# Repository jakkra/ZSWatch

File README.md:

# [zswatch.dev](https://zswatch.dev/)

<div align="center">

<sub>
  ZSWatch v4 CNC:ed Stainless Steel (left), Clear Resin 3D print (right)
</sub>
</div>

## Table of content

- [ZSWatch](#zswatch)
  - [Table of content](#table-of-content)
  - [About](#about)
  - [Features](#features)
    - [Hardware](#hardware)
      - [PCB](#pcb)
    - [Software](#software)
    - [Watchfaces](#watchfaces)
    - [Smartphone communication](#smartphone-communication)
      - [Pairing](#pairing)
      - [Android phone communication](#android-phone-communication)
      - [iOS device communication](#ios-device-communication)
    - [Enclosure/Casing](#enclosurecasing)
    - [Upcomming features](#upcomming-features)
  - [Charger/Dock](#chargerdock)
  - [Demos](#demos)
  - [Building or getting one](#building-or-getting-one)
  - [Environment, Compiling and running the code](#environment-compiling-and-running-the-code)
  - [Writing apps for the Application Manager](#writing-apps-for-the-application-manager)
  - [Licence GPL-3.0](#licence-gpl-30)
  - [Thanks](#thanks)
  - [Miscellaneous stuff](#miscellaneous-stuff)

## About

Smartwatch built from scratch, both hardware and software. Built on the [Zephyr™ Project](https://www.zephyrproject.org/) RTOS, hence the name **ZSWatch** - *Zephyr Smartwatch*.

<kbd></kbd>

https://github.com/jakkra/ZSWatch/assets/4318648/ec1a94fd-a682-4559-9e68-f3e5bfcbe682

## Features

### Hardware

- nRF5340 BLE chip ([u-blox NORA-B10 module](https://www.u-blox.com/en/product/nora-b1-series-open-cpu))
  - 128 MHz Dual core
  - 512 KB RAM
  - 1 MB Flash
  - 30 MHz SPI for display
- [240x240 round display](https://www.buydisplay.com/catalog/product/view/id/1849/s/240x240-round-ips-tft-lcd-display-1-28-capacitive-touch-circle-screen/) with touch screen
- IMU [Bosch BMI270](https://www.bosch-sensortec.com/media/boschsensortec/downloads/datasheets/bst-bmi270-ds000.pdf), with this one it's possible to do many fancy things such as navigation using gestures and the typical smartwatch wakeup by moving the arm so the display is viewable
- Bosch [BME688](https://www.bosch-sensortec.com/products/environmental-sensors/gas-sensors/bme688/) Environmental sensor with AI
- Bosch [BMP581](https://www.bosch-sensortec.com/products/environmental-sensors/pressure-sensors/bmp581/) High performance pressure sensor accuracy in units of ~20cm's
- ST [LIS2MDLTR](https://www.st.com/resource/en/datasheet/lis2mdl.pdf) Magnetometer
- Macronix [MX25U51245GZ4I00](https://www.mouser.de/datasheet/2/819/MX25U51245G_2c_1_8V_2c_512Mb_2c_v1_4-3371129.pdf) 64 MB external flash
- Broadcom [APDS-9306-065](https://docs.broadcom.com/docs/AV02-4755EN) Light Sensor for automatic brightness control
- Micro Crystal [RV-8263-C8](https://www.microcrystal.com/en/products/real-time-clock-rtc-modules/rv-8263-c8) RTC for time keeping and alarm functions
- Knowles [SPK0641HT4H-1](https://www.knowles.com/docs/default-source/model-downloads/spk0641ht4h-1-rev-a.pdf) I2S microphone for audio recording
- Nordic [nPM1300](https://docs.nordicsemi.com/category/npm1300-category) PMIC for power and system management
- Texas Instruments [TS3USB221A](https://www.ti.com/lit/ds/symlink/ts3usb221a.pdf?HQS=dis-mous-null-mousermode-dsf-pf-null-wwe&ts=1695813909306&ref_url=https%253A%252F%252Feu.mouser.com%252F) USB / SWD switch to provide a USB or SWD interface on the dock connector
- Option to not mount sensors to save BOM cost

#### PCB

A 4-layer board that measures 38mm in diameter is designed in KiCad. More info [here](https://github.com/jakkra/ZSWatch-HW).

<kbd></kbd>

### Software

- Bluetooth LE communications with [GadgetBridge](https://codeberg.org/Freeyourgadget/Gadgetbridge) Android app.
- Also support Bluetooth Direction Finding so the watch can act as a tag and is trackable using any [u-blox AoA antenna board](https://www.u-blox.com/en/product/ant-b10-antenna-board)
- Multiple Watchfaces showing:
  - Standard stuff such as time, date, battery
  - Weather
  - Step count
  - Number of unread notifications
  - Environmental data
  - ...
- Pop-up notifications
- [Application picker and app concept](#writing-apps-for-the-application-manager)
  - [Setting menu system, with easy extendability](app/src/applications/settings/)
  - [Music control app](app/src/applications/music_control/)
  - [Settings app](app/src/applications/settings/)
  - [Compass app](app/src/applications/compass/)
  - etc.
- Step counting
- Gestures
- And much more
...

### Watchfaces

The watch supports different watchfaces which can be changed dynamically. The watch also supports ESP32 watchfaces from [Felix Biego](https://github.com/fbiego). Please checkout [this](https://github.com/Kampi/esp32-lvgl-watchface) fork for more informations.

### Smartphone communication

#### Pairing

- In the watch go to `Settings` -> `Bluetooth` -> `Enable pairing`
- Now go reconnect to the watch from the Gadgetbridge app
- You should now be paired

#### Android phone communication

Fortunately, there is a great Android app called [GadgetBridge](https://codeberg.org/Freeyourgadget) that handles everything needed on the phone side, such as notifications management, music control and so much more. The ZSWatch right now pretends to be one of the supported Smart Watches in Gadgetbridge, following the same API as it does. In the future there may be a point in adding native support, we'll see.

#### iOS device communication

Apple exposes [Apple Notification Center Service](https://developer.apple.com/library/archive/documentation/CoreBluetooth/Reference/AppleNotificationCenterServiceSpecification/Specification/Specification.html) GATT server which handles notifications management on the phone side, music control is done in the same fashion using [Apple Media Service](https://developer.apple.com/library/archive/documentation/CoreBluetooth/Reference/AppleMediaService_Reference/Specification/Specification.html)... The ZSWatch communicates straight to the iOS with no extra Apps.

### Enclosure/Casing

3D printed casing with 3D printed buttons, option CNC:able casing in metal.

### Upcomming features

There are almost endless possibilities for features that could be implemented, see [here for full progress](https://github.com/users/jakkra/projects/1) and in GitHub issues.

## Charger/Dock

Option with and without onboard SEGGER J-Link OB debugger. As the debugger requires a license, this will only be available as part of a kit.

See more at [here](https://github.com/jakkra/ZSWatch-Dock).

## Demos

- [HTTP requests over BLE through Gadgetbridge](https://github.com/jakkra/ZSWatch/assets/4318648/12d6e754-ceb3-4efd-9a75-d207aaeb0e82)
- [Watchfaces](https://github.com/jakkra/ZSWatch/assets/4318648/13e43401-1c00-40ab-866f-e6518e61940d)

## Building or getting one

- Head over to the hardware repos for the [PCB](https://github.com/jakkra/ZSWatch-HW) and the [Dock](https://github.com/jakkra/ZSWatch-Dock) for information about ordering the PCBs and assembly from PCBWay
- Go to the [Wiki](https://github.com/jakkra/ZSWatch/wiki/Case,-3D-printing-and-assembling) for information how to print parts and assemble ZSWatch

Some things are still in progress:

- [Building instructions in Wiki](https://github.com/jakkra/ZSWatch/wiki/Case,-3D-printing-and-assembling)
- Dock casing

If you are interested in a kit or want to get notified when the missing parts above are resolved, fill in your **[mail here](https://zswatch.dev/)** and we'll send a reminder when it's ready.

**Or** if you want to get notified for releases and when the missing parts are finished simply press the `Watch` button (next to Fork and Star) -> `Custom` -> `Releases` and you will see in your feed when it's officially released.

## Environment, Compiling and running the code

See [Wiki page about Start Developing](https://github.com/jakkra/ZSWatch/wiki/Start-Developing).

## Writing apps for the Application Manager

See [Wiki page about apps](https://github.com/jakkra/ZSWatch/wiki/Apps).

## Licence GPL-3.0

The main difference from MIT is now that if anyone wants to build something more with this, then they need to also open source their changes back to the project, which I think this is fair. This is so everyone can benefit from those improvements. If you think this is wrong free to contact me and I'm open to change the LICENCE.

## Thanks

### Funding

This project is partly funded through [NGI0 Commons Fund](https://nlnet.nl/commonsfund), a fund established by [NLnet](https://nlnet.nl) with financial support from the European Commission's [Next Generation Internet](https://ngi.eu) program. Learn more at the [NLnet project page](https://nlnet.nl/project/ZSWatch).

### Support

<p align="left">

</p>

**PCBWay** for sponsoring the manufacturing and assembly of some prototype PCBs. PCBWay is the recommended manufacturer for PCBs and assembly of ZSWatch.

**SEGGER** for supporting SEGGER-OB licenses that make the dock a fully functional programmer and debugger for ZSWatch. Thanks to this, the project is much more approachable for persons without a J-Link debugger, letting them have full development and debugging capabilities.

## Miscellaneous stuff

- [Watch my presentation at Zephyr Developer Summit 2023](https://www.youtube.com/watch?v=MmCzV0jV9hs)

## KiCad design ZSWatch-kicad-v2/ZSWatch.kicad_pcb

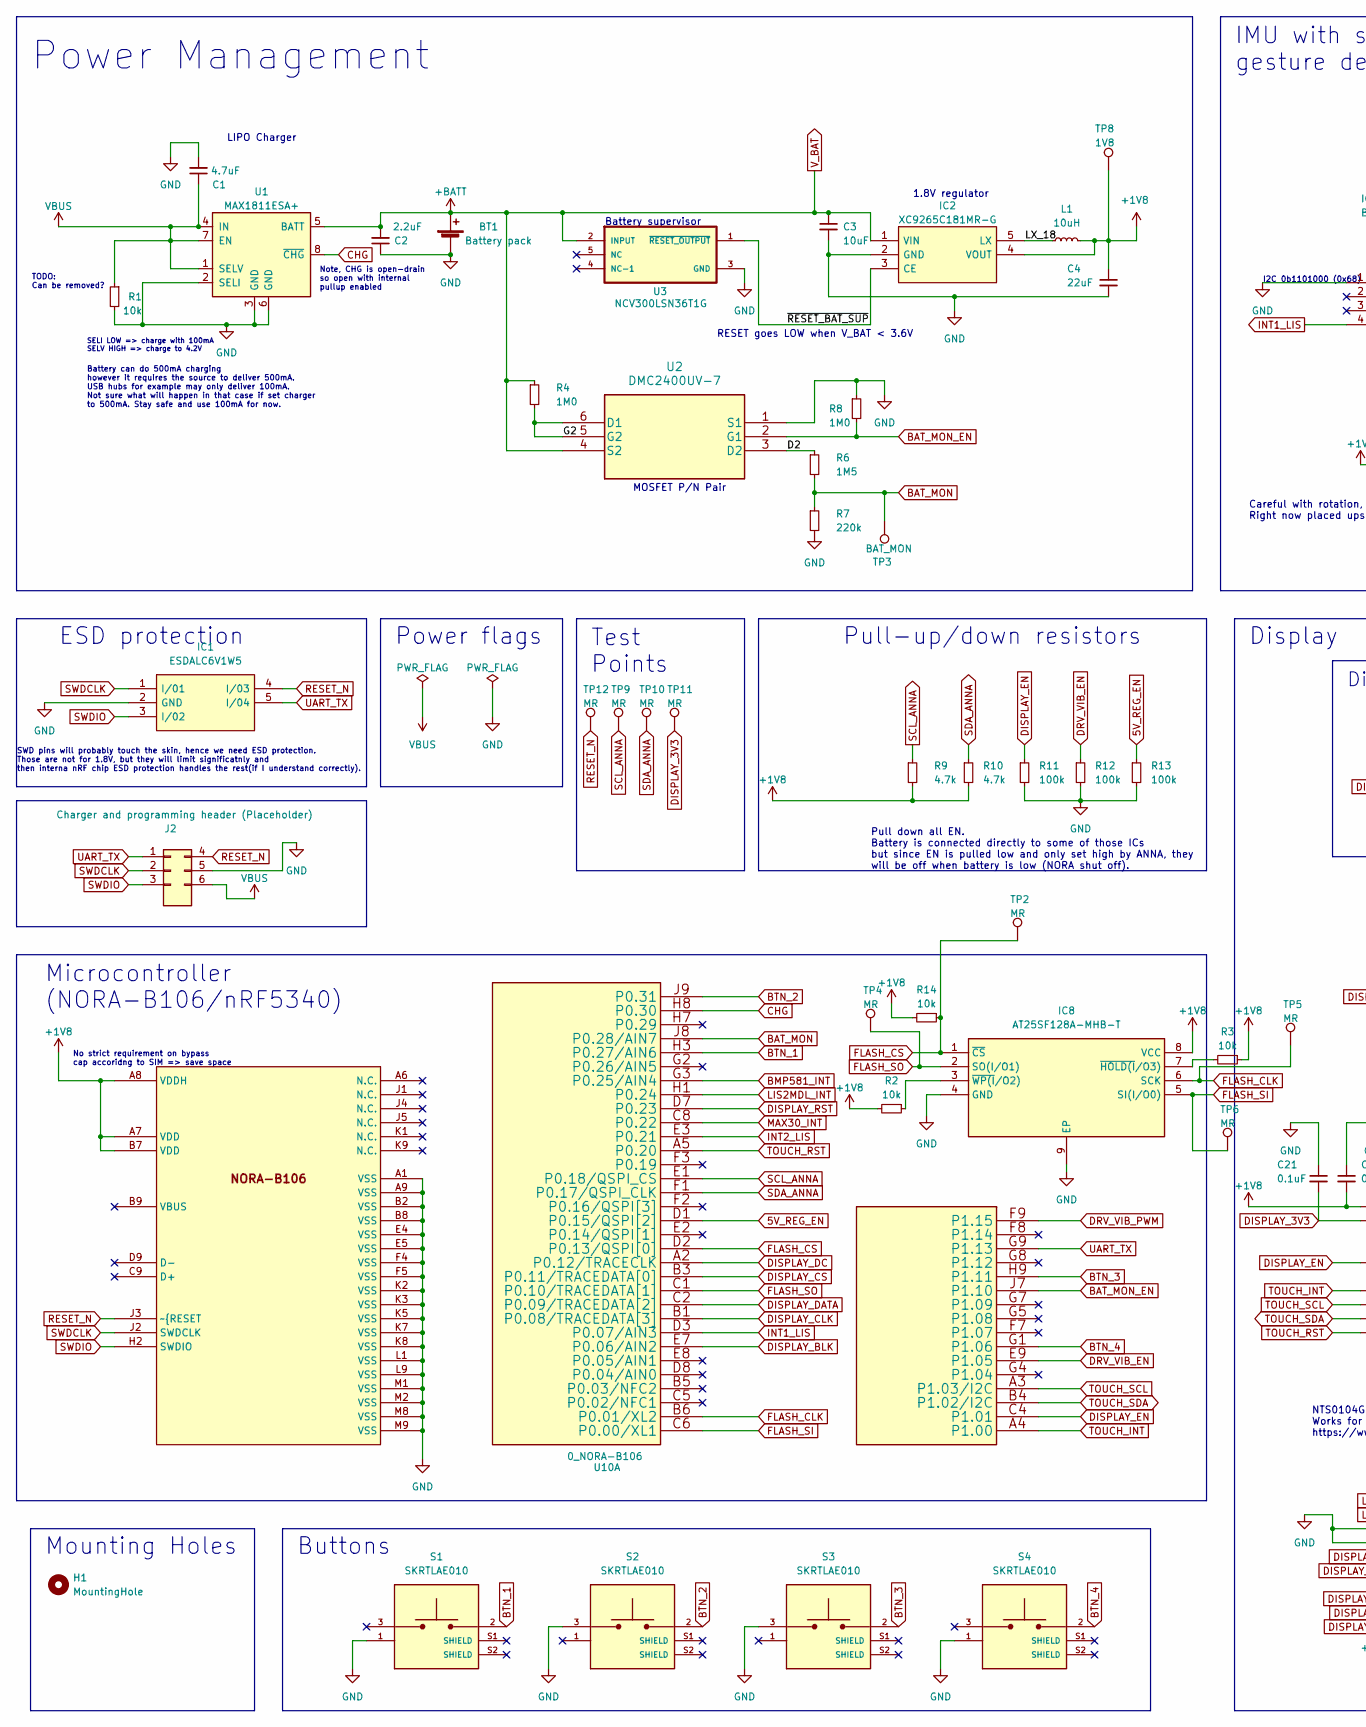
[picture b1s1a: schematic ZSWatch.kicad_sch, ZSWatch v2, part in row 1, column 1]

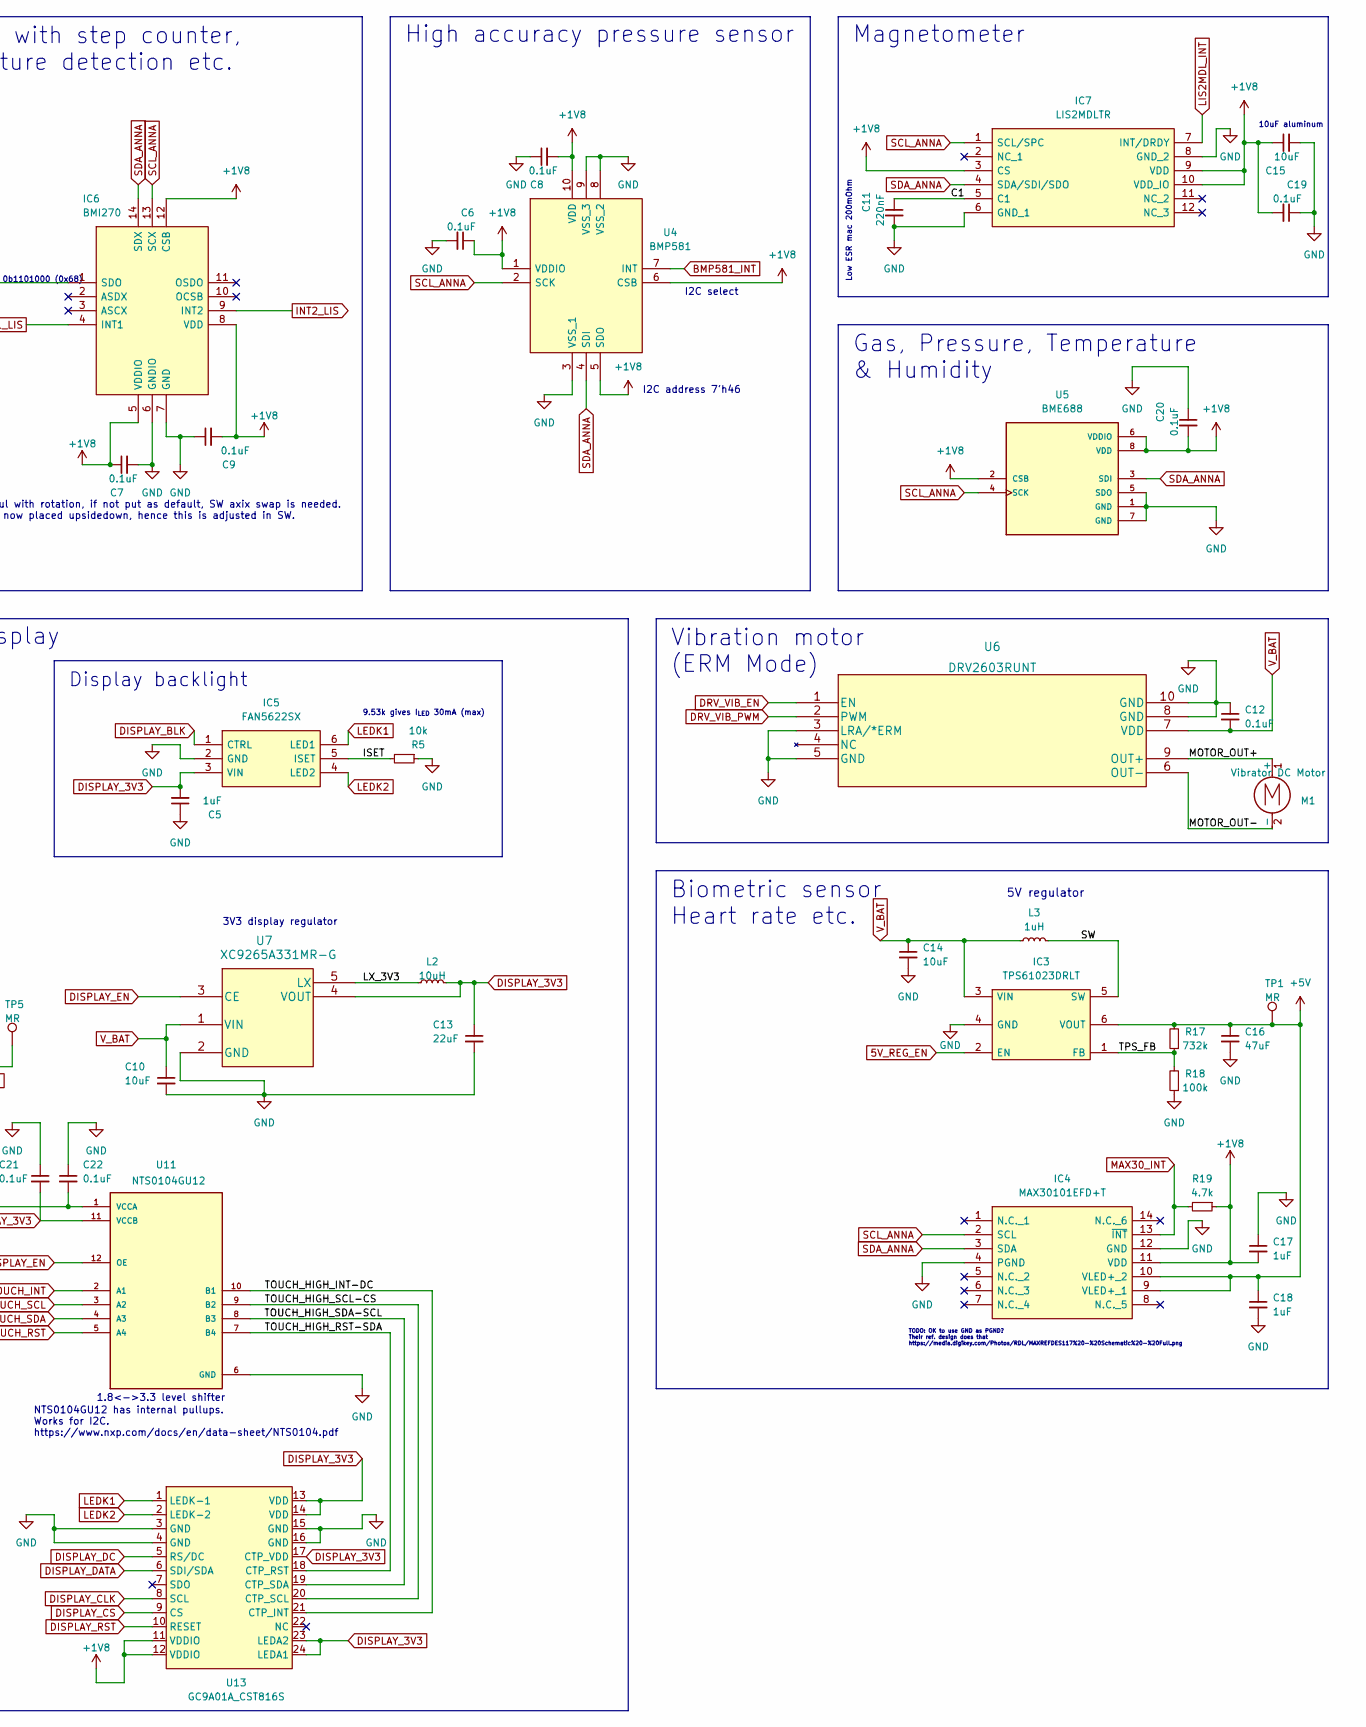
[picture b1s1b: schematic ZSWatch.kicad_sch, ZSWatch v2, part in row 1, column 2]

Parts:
BT1: Battery pack; SolderWire-0.1sqmm_1x02_P3.6mm_D0.4mm_OD1mm
C1: 4.7uF; C_0603_1608Metric
C2: 2.2uF; C_0603_1608Metric
C3, C10, C14, C15: 10uF; C_0603_1608Metric
C4, C13: 22uF; C_0603_1608Metric
C5, C17, C18: 1uF; C_0603_1608Metric
C6, C7, C8, C9, C12, C19, C20, C21, C22: 0.1uF; C_0603_1608Metric
C11: 220nF; C_0603_1608Metric
C16: 47uF; C_0603_1608Metric
H1: MountingHole; MountingHole_3.5mm_Pad_Via
IC1: ESDALC6V1W5; SOT65P210X110-5L; Mouser Part Number 511-ESDALC6V1W5
IC2: XC9265C181MR-G; SOT95P280X130-5N; Mouser Part Number 865-XC9265C181MR-G
IC3: TPS61023DRLT; SOTFL50P160X60-6N; Mouser Part Number 595-TPS61023DRLT
IC4: MAX30101EFD+T; 14-LEAD-OESIP; Mouser Part Number 700-MAX30101EFD+T
IC5: FAN5622SX; SOT95P280X110-6N; Mouser Part Number 512-FAN5622SX
IC6: BMI270; QFN50P300X250X87-14N; Mouser Part Number 262-BMI270
IC7: LIS2MDLTR; LGA-12; Mouser Part Number 511-LIS2MDLTR
IC8: AT25SF128A-MHB-T; SON127P600X500X60-9N-D; Manufacturer_Part_Number AT25SF128A-MHB-T; Mouser Part Number 988-AT25SF128A-MHB-T
J2: Charger and programming header (Placeholder); rtlecs-6-pin-2-54
L1, L2: 10uH; L_0603_1608Metric
L3: 1uH; L_0603_1608Metric
M1: Vibrator DC Motor; TestPoint_2Pads_Pitch2.54mm_Drill0.8mm
R1, R3, R5: 10k; R_0603_1608Metric
R2, R14: 10k; R_0402_1005Metric
R4, R8: 1M0; R_0603_1608Metric
R6: 1M5; R_0603_1608Metric
R7: 220k; R_0603_1608Metric
R9, R10, R19: 4.7k; R_0603_1608Metric
R11, R12, R13, R18: 100k; R_0603_1608Metric
R17: 732k; R_0603_1608Metric
S1, S2, S3, S4: SKRTLAE010; SW_SKRTLAE010; PARTREV --
TP1, TP2, TP4, TP5, TP6, TP9, TP10, TP11, TP12: MR; TestPoint_Pad_D1.0mm
TP3: BAT_MON; TestPoint_Pad_D1.0mm
TP8: 1V8; TestPoint_Pad_D1.0mm
U1: MAX1811ESA+; SOIC127P600X175-8N
U2: DMC2400UV-7
U3: NCV300LSN36T1G; SOT95P275X110-5N
U4: BMP581; Mouser Part Number 262-BMP581
U5: BME688; IC_BME688; PARTREV 1.0
U6: DRV2603RUNT
U7: XC9265A331MR-G; SOT95P280X130-5N
U10: 0_NORA-B106; NORA_LGA82R_1430X1040X180_ANT; MANUFACTURER P/N NORA-B106-00B
U11: NTS0104GU12; HPA01164RUTR; PARTREV 4210580/C 06/12
U13: GC9A01A_CST816S; ER-24F24-04

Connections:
5V_REG_EN: IC3.2 (EN), R13.1, U10.D1 (P0.15/QSPI[2])
+1V8: C4.1, C6.1, C7.1, C8.2, C9.2, C15.1, C17.2, C19.2, C20.2, C22.2, IC2.4 (VOUT), IC4.11 (VDD), IC6.5 (VDDIO), IC6.8 (VDD), IC6.12 (CSB), IC7.3 (CS), IC7.9 (VDD), IC7.10 (VDD_IO), IC8.8 (VCC), L1.2, R2.2, R3.1, R9.2, R10.2, R14.2, R19.1, TP8.1, U4.1 (VDDIO), U4.5 (SDO), U4.6 (CSB), U4.10 (VDD), U5.2 (CSB), U5.6 (VDDIO), U5.8 (VDD), U10.A7 (VDD), U10.A8 (VDDH), U10.B7 (VDD), U11.1 (VCCA), U13.11 (VDDIO), U13.12 (VDDIO)
+5V: C16.1, C18.1, IC3.6 (VOUT), IC4.9 (VLED+_1), IC4.10 (VLED+_2), R17.2, TP1.1
/C1: C11.1, IC7.5 (C1)
/D2: R6.1, U2.3 (D2)
/G2: R4.2, U2.5 (G2), U2.6 (D1)
/ISET: IC5.5 (ISET), R5.2
/LX_3V3: L2.1, U7.5 (LX)
/LX_18: IC2.5 (LX), L1.1
/MOTOR_OUT+: M1.1 (+), U6.9 (OUT+)
/MOTOR_OUT-: M1.2 (-), U6.6 (OUT-)
/SW: IC3.5 (SW), L3.2
/TOUCH_HIGH_INT-DC: U11.10 (B1), U13.21 (CTP_INT)
/TOUCH_HIGH_RST-SDA: U11.7 (B4), U13.18 (CTP_RST)
/TOUCH_HIGH_SCL-CS: U11.9 (B2), U13.20 (CTP_SCL)
/TOUCH_HIGH_SDA-SCL: U11.8 (B3), U13.19 (CTP_SDA)
/TPS_FB: IC3.1 (FB), R17.1, R18.2
/~RESET_BAT_SUP: IC2.3 (CE), U3.1 (~RESET_OUTPUT)
BAT_MON: R6.2, R7.1, TP3.1, U10.J8 (P0.28/AIN7)
BAT_MON_EN: R8.2, U2.2 (G1), U10.J7 (P1.10)
BMP581_INT: U4.7 (INT), U10.G3 (P0.25/AIN4)
BTN_1: S1.2, U10.H3 (P0.27/AIN6)
BTN_2: S2.2, U10.J9 (P0.31)
BTN_3: S3.2, U10.H9 (P1.11)
BTN_4: S4.2, U10.G1 (P1.06)
CHG: U1.8 (~CHG), U10.H8 (P0.30)
DISPLAY_3V3: C5.2, C13.1, C21.2, IC5.3 (VIN), L2.2, TP11.1, U7.4 (VOUT), U11.11 (VCCB), U13.13 (VDD), U13.14 (VDD), U13.17 (CTP_VDD), U13.23 (LEDA2), U13.24 (LEDA1)
DISPLAY_BLK: IC5.1 (CTRL), U10.E7 (P0.06/AIN2)
DISPLAY_CLK: U10.B1 (P0.08/TRACEDATA[3]), U13.8 (SCL)
DISPLAY_CS: U10.B3 (P0.11/TRACEDATA[0]), U13.9 (CS)
DISPLAY_DATA: U10.C2 (P0.09/TRACEDATA[2]), U13.6 (SDI/SDA)
DISPLAY_DC: U10.A2 (P0.12/TRACECLK), U13.5 (RS/DC)
DISPLAY_EN: R11.1, U7.3 (CE), U10.C4 (P1.01), U11.12 (OE)
DISPLAY_RST: U10.D7 (P0.23), U13.10 (RESET)
DRV_VIB_EN: R12.1, U6.1 (EN), U10.E9 (P1.05)
DRV_VIB_PWM: U6.2 (PWM), U10.F9 (P1.15)
FLASH_CLK: IC8.6 (SCK), TP5.1, U10.B6 (P0.01/XL2)
FLASH_CS: IC8.1 (~CS), R14.1, TP2.1, U10.D2 (P0.13/QSPI[0])
FLASH_SI: IC8.5 (SI(I/O0)), TP6.1, U10.C6 (P0.00/XL1)
FLASH_SO: IC8.2 (SO(I/O1)), TP4.1, U10.C1 (P0.10/TRACEDATA[1])
GND: BT1.2 (-), C1.2, C2.1, C3.2, C4.2, C5.1, C6.2, C7.2, C8.1, C9.1, C10.2, C11.2, C12.1, C13.2, C14.2, C15.2, C16.2, C17.1, C18.2, C19.1, C20.1, C21.1, C22.1, IC1.2 (GND), IC2.2 (GND), IC3.4 (GND), IC4.4 (PGND), IC4.12 (GND), IC5.2 (GND), IC6.1 (SDO), IC6.6 (GNDIO), IC6.7 (GND), IC7.6 (GND_1), IC7.8 (GND_2), IC8.4 (GND), IC8.9 (EP), J2.5, R1.2, R5.1, R7.2, R8.1, R11.2, R12.2, R13.2, R18.1, S1.1, S2.3, S3.3, S4.1, U1.2 (SELI), U1.3 (GND), U1.6 (GND), U2.1 (S1), U3.3 (GND), U4.3 (VSS_1), U4.8 (VSS_2), U4.9 (VSS_3), U5.1 (GND), U5.5 (SDO), U5.7 (GND), U6.3 (LRA/*ERM), U6.5 (GND), U6.8 (GND), U6.10 (GND), U7.2 (GND), U10.A1 (VSS), U10.A9 (VSS), U10.B2 (VSS), U10.B8 (VSS), U10.E4 (VSS), U10.E5 (VSS), U10.F4 (VSS), U10.F5 (VSS), U10.K2 (VSS), U10.K3 (VSS), U10.K5 (VSS), U10.K7 (VSS), U10.K8 (VSS), U10.L1 (VSS), U10.L9 (VSS), U10.M1 (VSS), U10.M2 (VSS), U10.M8 (VSS), U10.M9 (VSS), U11.6 (GND), U13.3 (GND), U13.4 (GND), U13.15 (GND), U13.16 (GND)
INT1_LIS: IC6.4 (INT1), U10.D3 (P0.07/AIN3)
INT2_LIS: IC6.9 (INT2), U10.E3 (P0.21)
LEDK1: IC5.6 (LED1), U13.1 (LEDK-1)
LEDK2: IC5.4 (LED2), U13.2 (LEDK-2)
LIS2MDL_INT: IC7.7 (INT/DRDY), U10.H1 (P0.24)
MAX30_INT: IC4.13 (~INT), R19.2, U10.C8 (P0.22)
unnamed: IC8.7 (~HOLD(I/O3)), R3.2
unnamed: IC8.3 (~WP(I/O2)), R2.1
RESET_N: IC1.4 (I/03), J2.4, TP12.1, U10.J3 (~{RESET)
SCL_ANNA: IC4.2 (SCL), IC6.13 (SCX), IC7.1 (SCL/SPC), R9.1, TP9.1, U4.2 (SCK), U5.4 (SCK), U10.E1 (P0.18/QSPI_CS)
SDA_ANNA: IC4.3 (SDA), IC6.14 (SDX), IC7.4 (SDA/SDI/SDO), R10.1, TP10.1, U4.4 (SDI), U5.3 (SDI), U10.F1 (P0.17/QSPI_CLK)
SWDCLK: IC1.1 (I/01), J2.2, U10.J2 (SWDCLK)
SWDIO: IC1.3 (I/02), J2.3, U10.H2 (SWDIO)
TOUCH_INT: U10.A4 (P1.00), U11.2 (A1)
TOUCH_RST: U10.A5 (P0.20), U11.5 (A4)
TOUCH_SCL: U10.A3 (P1.03/I2C), U11.3 (A2)
TOUCH_SDA: U10.B4 (P1.02/I2C), U11.4 (A3)
UART_TX: IC1.5 (I/04), J2.1, U10.G9 (P1.13)
VBUS: C1.1, J2.6, R1.1, U1.1 (SELV), U1.4 (IN), U1.7 (EN)
V_BAT: BT1.1 (+), C2.2, C3.1, C10.1, C12.2, C14.1, IC2.1 (VIN), IC3.3 (VIN), L3.1, R4.1, U1.5 (BATT), U2.4 (S2), U3.2 (INPUT), U6.7 (VDD), U7.1 (VIN)

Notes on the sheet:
Test Points
Display backlight
Battery can do 500mA charging however it requires the source to deliver 500mA. USB hubs for example may only deliver 100mA. Not sure what will happen in that case if set charger to 500mA. Stay safe and use 100mA for now.
1.8<->3.3 level shifter
I2C select
Biometric sensor Heart rate etc.
Gas, Pressure, Temperature & Humidity
High accuracy pressure sensor
3V3 display regulator
Pull-up/down resistors
MOSFET P/N Pair
Power Management
SELI LOW => charge with 100mA SELV HIGH => charge to 4.2V
Battery supervisor
RESET goes LOW when V_BAT < 3.6V
I2C address 7'h46
Low ESR mac 200mOhm
_{I2C 0b1101000 (0x68)}
NTS0104GU12 has internal pullups. Works for I2C. https://www.nxp.com/docs/en/data-sheet/NTS0104.pdf
TODO: Can be removed?
Buttons
Microcontroller (NORA-B106/nRF5340)
TODO: OK to use GND as PGND? Their ref. design does that https://media.digikey.com/Photos/RDL/MAXREFDES117%20-%20Schematic%20-%20Full.png
Note, CHG is open-drain so open with internal pullup enabled
No strict requirement on bypass cap accoridng to SIM => save space
Power flags
9.53k gives I_{LED} 30mA (max)
Magnetometer
SWD pins will probably touch the skin, hence we need ESD protection. Those are not for 1.8V, but they will limit significatnly and then interna nRF chip ESD protection handles the rest(if I understand correctly).
Pull down all EN. Battery is connected directly to some of those ICs but since EN is pulled low and only set high by ANNA, they will be off when battery is low (NORA shut off).
Careful with rotation, if not put as default, SW axix swap is needed. Right now placed upsidedown, hence this is adjusted in SW.
IMU with step counter, gesture detection etc.
LIPO Charger
5V regulator
ESD protection
Vibration motor (ERM Mode)
Mounting Holes
Display
10uF aluminum
1.8V regulator

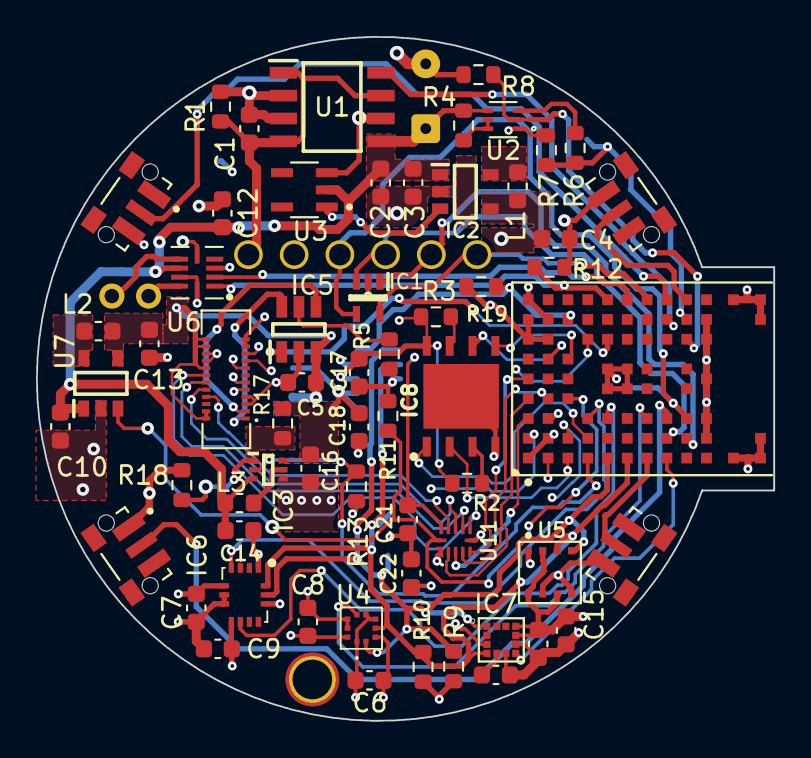
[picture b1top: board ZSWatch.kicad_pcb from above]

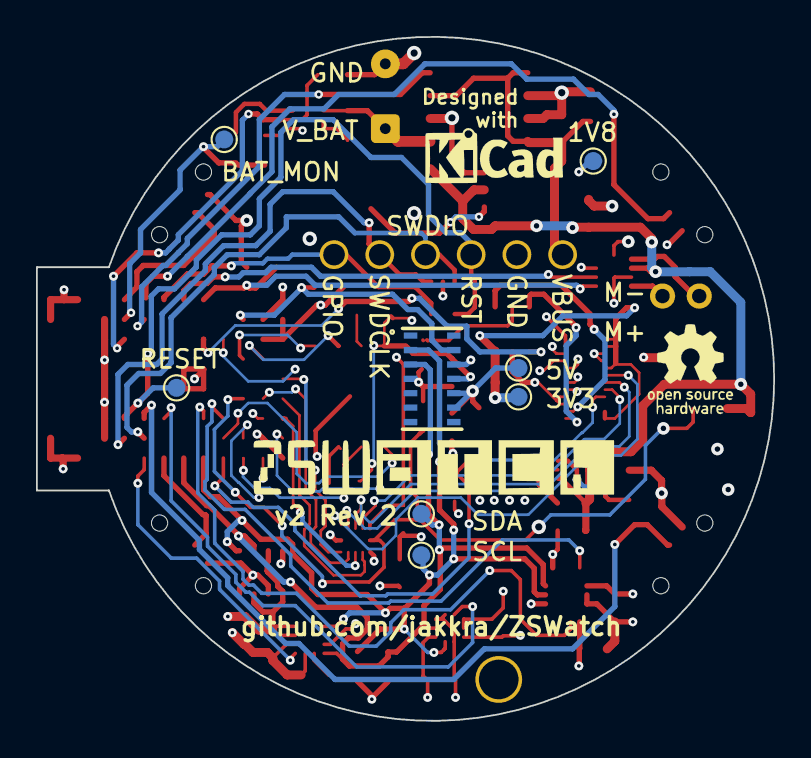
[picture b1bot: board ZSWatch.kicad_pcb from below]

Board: 4 copper layers, 41.0 x 38.0 mm, 73 parts (9 on the bottom side), 61 nets.

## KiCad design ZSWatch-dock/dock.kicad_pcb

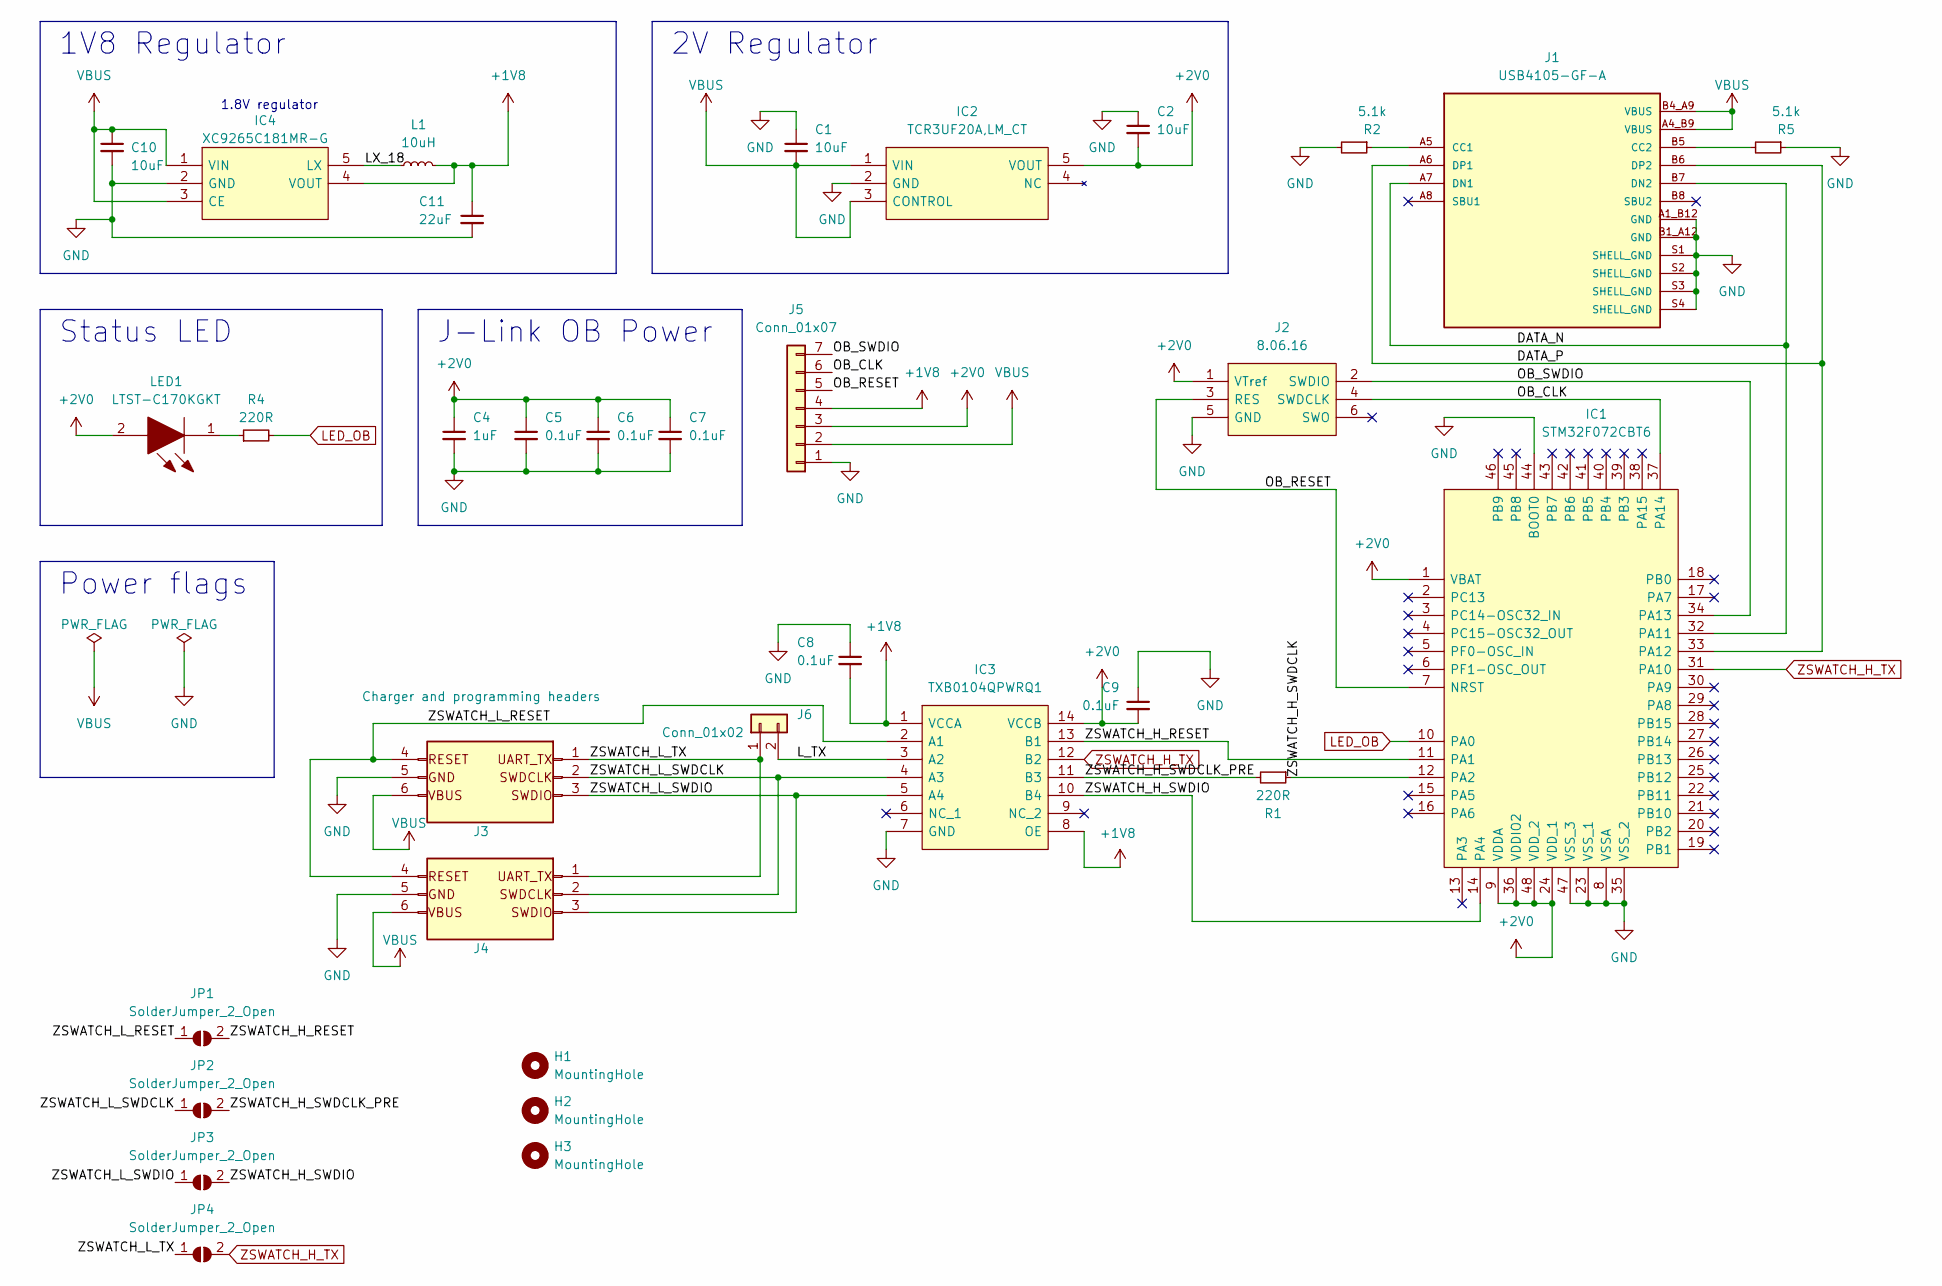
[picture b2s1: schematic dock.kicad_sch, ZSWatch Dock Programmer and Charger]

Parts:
C1, C2, C10: 10uF; C_0603_1608Metric
C4: 1uF; C_0603_1608Metric
C5, C6, C7, C8, C9: 0.1uF; C_0603_1608Metric
C11: 22uF; C_0603_1608Metric
H1, H2, H3: MountingHole; MountingHole_2.2mm_M2
IC1: STM32F072CBT6; QFP50P900X900X160-48N; Mouser Part Number 511-STM32F072CBT6
IC2: TCR3UF20A,LM_CT; TCR3UF20ALMCT; Mouser Part Number 757-TCR3UF20ALMCT
IC3: TXB0104QPWRQ1; SOP65P640X120-14N; Mouser Part Number 595-TXB0104QPWRQ1
IC4: XC9265C181MR-G; SOT95P280X130-5N; Mouser Part Number 865-XC9265C181MR-G
J1: USB4105-GF-A; GCT_USB4105-GF-A; PARTREV A3
J2: 8.06.16; 80616; Mouser Part Number 943-8.06.16
J3: Charger and programming headers; rtlecs-6-pin-2-54
J4: Charger and programming header; rtlecs-6-pin-2-54
J5: Conn_01x07; PinHeader_1x07_P2.54mm_Horizontal
J6: Conn_01x02; SolderJumper-2_P1.3mm_Bridged_Pad1.0x1.5mm
JP1, JP2, JP3, JP4: SolderJumper_2_Open; SolderJumper-2_P1.3mm_Open_RoundedPad1.0x1.5mm
L1: 10uH; L_0603_1608Metric
LED1: LTST-C170KGKT; LEDC2012X110N; Mouser Part Number 859-LTST-C170KGKT
R1, R4: 220R; R_0603_1608Metric
R2, R5: 5.1k; R_0603_1608Metric

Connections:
+1V8: C8.2, C11.1, IC3.1 (VCCA), IC3.8 (OE), IC4.4 (VOUT), J5.4, L1.2
+2V0: C2.2, C4.1, C5.1, C6.1, C7.1, C9.2, IC1.1 (VBAT), IC1.9 (VDDA), IC1.24 (VDD_1), IC1.36 (VDDIO2), IC1.48 (VDD_2), IC2.5 (VOUT), IC3.14 (VCCB), J2.1 (VTref), J5.3, LED1.2
/DATA_N: IC1.32 (PA11), J1.A7 (DN1), J1.B7 (DN2)
/DATA_P: IC1.33 (PA12), J1.A6 (DP1), J1.B6 (DP2)
/LX_18: IC4.5 (LX), L1.1
/L_TX: IC3.3 (A2), J6.2
/OB_CLK: IC1.37 (PA14), J2.4 (SWDCLK), J5.6
/OB_RESET: IC1.7 (NRST), J2.3 (RES), J5.5
/OB_SWDIO: IC1.34 (PA13), J2.2 (SWDIO), J5.7
/ZSWATCH_H_RESET: IC1.11 (PA1), IC3.13 (B1), JP1.2 (B)
/ZSWATCH_H_SWDCLK: IC1.12 (PA2), R1.1
/ZSWATCH_H_SWDCLK_PRE: IC3.11 (B3), JP2.2 (B), R1.2
/ZSWATCH_H_SWDIO: IC1.14 (PA4), IC3.10 (B4), JP3.2 (B)
/ZSWATCH_L_RESET: IC3.2 (A1), J3.4, J4.4, JP1.1 (A)
/ZSWATCH_L_SWDCLK: IC3.4 (A3), J3.2, J4.2, JP2.1 (A)
/ZSWATCH_L_SWDIO: IC3.5 (A4), J3.3, J4.3, JP3.1 (A)
/ZSWATCH_L_TX: J3.1, J4.1, J6.1, JP4.1 (A)
GND: C1.1, C2.1, C4.2, C5.2, C6.2, C7.2, C8.1, C9.1, C10.2, C11.2, IC1.8 (VSSA), IC1.23 (VSS_1), IC1.35 (VSS_2), IC1.44 (BOOT0), IC1.47 (VSS_3), IC2.2 (GND), IC3.7 (GND), IC4.2 (GND), J1.A1_B12 (GND), J1.B1_A12 (GND), J1.S1 (SHELL_GND), J1.S2 (SHELL_GND), J1.S3 (SHELL_GND), J1.S4 (SHELL_GND), J2.5 (GND), J3.5, J4.5, J5.1, R2.2, R5.1
LED_OB: IC1.10 (PA0), R4.2
unnamed: J1.A5 (CC1), R2.1
unnamed: J1.B5 (CC2), R5.2
unnamed: LED1.1, R4.1
VBUS: C1.2, C10.1, IC2.1 (VIN), IC2.3 (CONTROL), IC4.1 (VIN), IC4.3 (CE), J1.A4_B9 (VBUS), J1.B4_A9 (VBUS), J3.6, J4.6, J5.2
ZSWATCH_H_TX: IC1.31 (PA10), IC3.12 (B2), JP4.2 (B)

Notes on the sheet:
Status LED
1.8V regulator
1V8 Regulator
Power flags
J-Link OB Power
2V Regulator

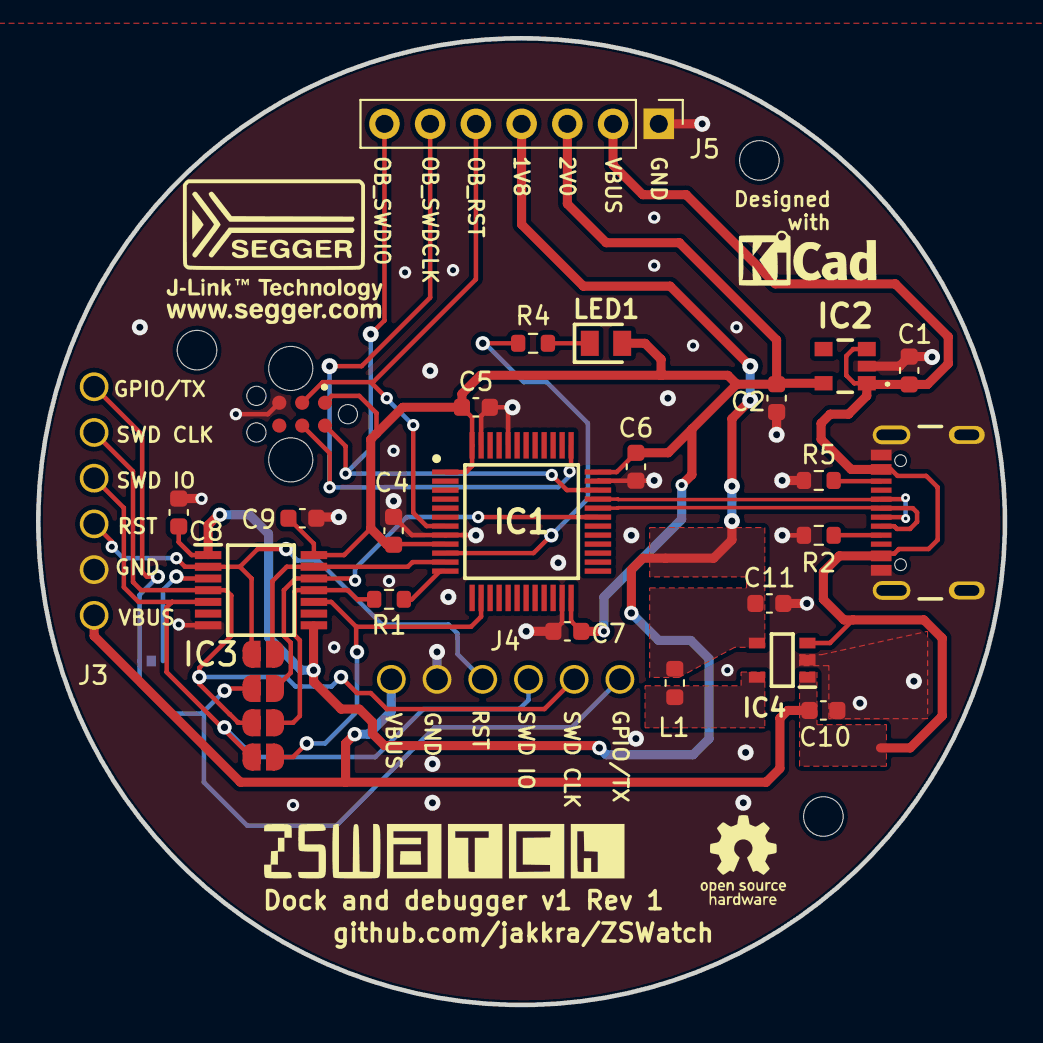
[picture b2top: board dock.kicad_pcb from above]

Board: 2 copper layers, 53.7 x 53.7 mm, 33 parts (1 on the bottom side), 24 nets.

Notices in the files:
README.md:
License: GPL 3.0
parts and their libraries:
Copyright 2021 Accelerated Designs. All rights reserved.
